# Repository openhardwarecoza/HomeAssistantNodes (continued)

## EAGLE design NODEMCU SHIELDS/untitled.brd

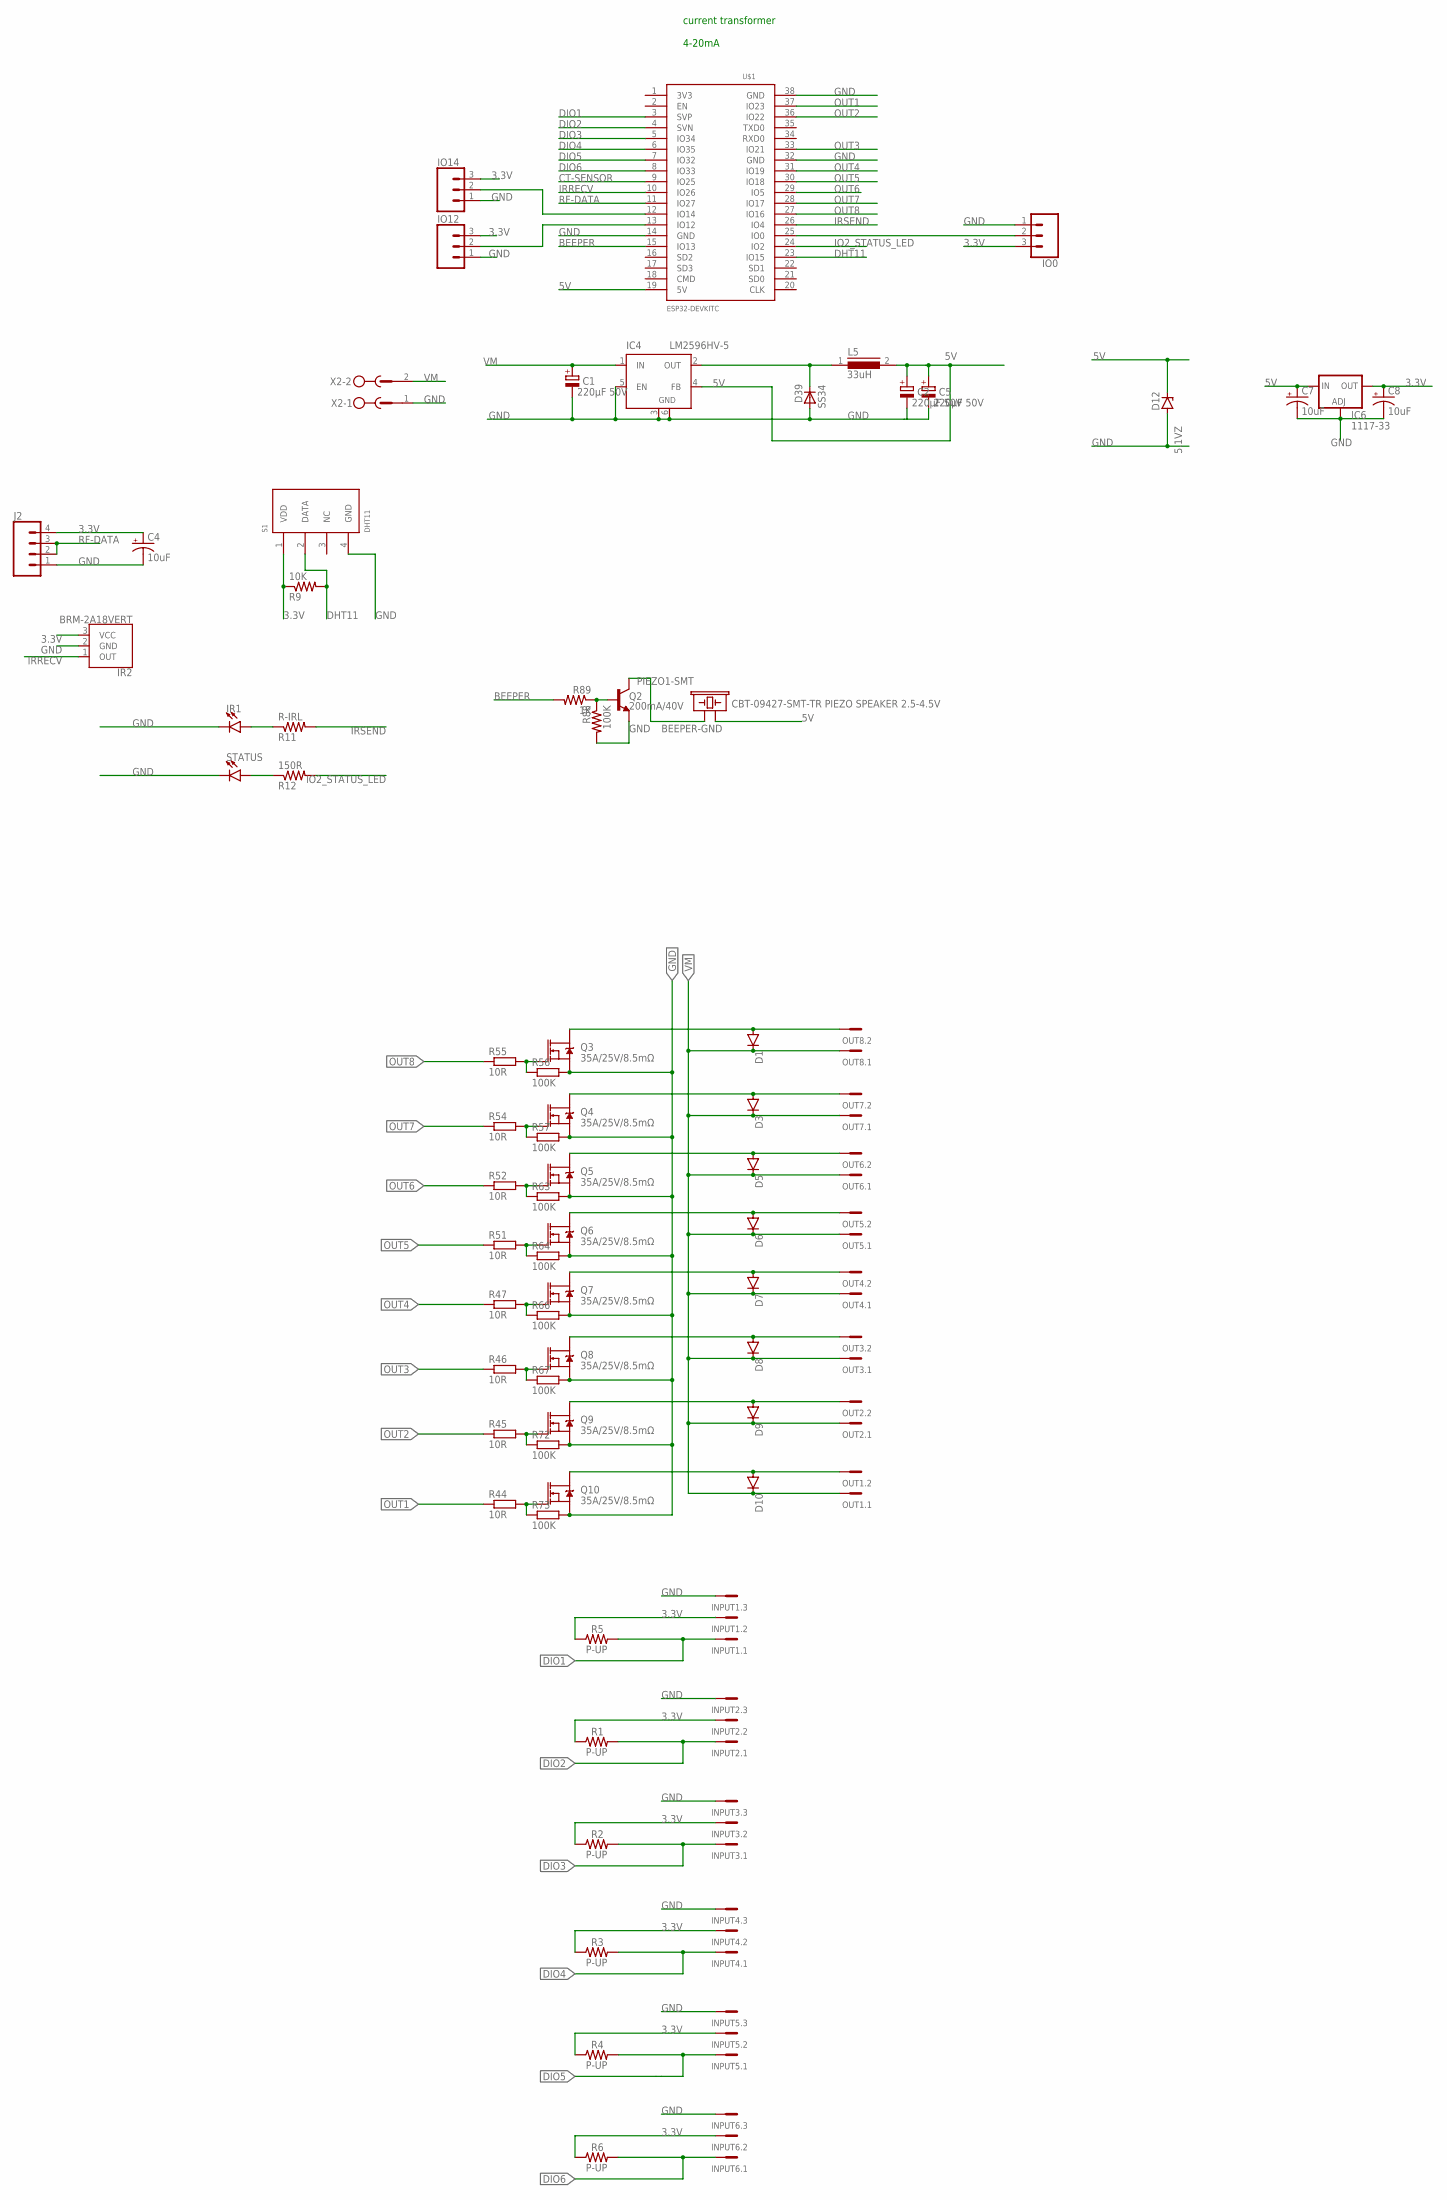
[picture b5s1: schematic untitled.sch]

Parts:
C1, C2, C5: 220µF 50V; E3,5-8
C4, C7, C8: 10uF; CPOL-RADIAL-10UF-25V
D1, D3, D5, D6, D7, D8, D9, D10: 1N4148DO35-7; DO35-7
D12: 5.1VZ; SMB
D39: SS34; SOD87
IC4: LM2596HV-5; TO263-5
IC6: 1117-33; SOT223
INPUT1, INPUT2, INPUT3, INPUT4, INPUT5, INPUT6: MCV3
IO0, IO12, IO14: CONN_03LOCK; 1X03_LOCK
IR1: LED3MM; LED_3MM
IR2: BRM-2A18VERT; BRM-2508_VERT
J2: CONN_04LOCK; 1X04_LOCK
L5: 33uH; DR127
OUT1, OUT2, OUT3, OUT4, OUT5, OUT6, OUT7, OUT8: MCV2
PIEZO1-SMT: CBT-09427-SMT-TR PIEZO SPEAKER 2.5-4.5V; BUZZER-12MM
Q2: 200mA/40V; TO-92
Q3, Q4, Q5, Q6, Q7, Q8, Q9, Q10: 35A/25V/8.5mΩ; DPAK
R1, R2, R3, R4, R5, R6: P-UP; 0204/7
R9: 10K; 0204/7
R11: R-IRL; 0204/7
R12: 150R; 0204/7
R44, R45, R46, R47, R51, R52, R54, R55: 10R; 0204/7
R56, R57, R63, R64, R66, R67, R72, R73, R88: 100K; 0204/7
R89: 1K; 0204/7
S1: DHT11
STATUS: LED3MM; LED_3MM
U$1: ESP32NODEMCU
X2: MSTBV2

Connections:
3.3V: C4.1 (+), C8.1 (+), IC6.4 (OUT), INPUT1.2, INPUT2.2, INPUT3.2, INPUT4.2, INPUT5.2, INPUT6.2, IO0.3, IO12.3, IO14.3, IR2.3 (VCC), J2.4, R1.1, R2.1, R3.1, R4.1, R5.1, R6.1, R9.1, S1.1 (VDD)
5V: C2.+, C5.+, C7.1 (+), D12.C, IC4.4 (FB), IC6.3 (IN), L5.2, PIEZO1-SMT.+ (1), U$1.19 (5V)
BEEPER: R89.2, U$1.15 (IO13)
BEEPER-GND: PIEZO1-SMT.- (2), Q2.3 (C)
CT-SENSOR: U$1.9 (IO25)
DHT11: R9.2, S1.2 (DATA), U$1.23 (IO15)
DIO1: INPUT1.1, R5.2, U$1.3 (SVP)
DIO2: INPUT2.1, R1.2, U$1.4 (SVN)
DIO3: INPUT3.1, R2.2, U$1.5 (IO34)
DIO4: INPUT4.1, R3.2, U$1.6 (IO35)
DIO5: INPUT5.1, R4.2, U$1.7 (IO32)
DIO6: INPUT6.1, R6.2, U$1.8 (IO33)
GND: C1.-, C2.-, C4.2 (-), C5.-, C7.2 (-), C8.2 (-), D12.A, D39.2 (A), IC4.3 (GND), IC4.5 (EN), IC4.6 (GND), IC6.1 (ADJ), INPUT1.3, INPUT2.3, INPUT3.3, INPUT4.3, INPUT5.3, INPUT6.3, IO0.1, IO12.1, IO14.1, IR1.K (C), IR2.2 (GND), J2.1, Q2.1 (E), Q3.3 (S), Q4.3 (S), Q5.3 (S), Q6.3 (S), Q7.3 (S), Q8.3 (S), Q9.3 (S), Q10.3 (S), R56.2, R57.2, R63.2, R64.2, R66.2, R67.2, R72.2, R73.2, R88.2, S1.4 (GND), STATUS.K (C), U$1.14 (GND), U$1.32 (GND), U$1.38 (GND), X2.1
IO2_STATUS_LED: R12.2, U$1.24 (IO2)
IRRECV: IR2.1 (OUT), U$1.10 (IO26)
IRSEND: R11.2, U$1.26 (IO4)
unnamed: R12.1, STATUS.A
unnamed: IO0.2, U$1.25 (IO0)
unnamed: IO12.2, U$1.13 (IO12)
unnamed: IO14.2, U$1.12 (IO14)
unnamed: D9.A, OUT2.2, Q9.4 (D)
unnamed: IR1.A, R11.1
unnamed: Q2.2 (B), R88.1, R89.1
unnamed: Q10.1 (G), R44.2, R73.1
unnamed: Q9.1 (G), R45.2, R72.1
unnamed: Q8.1 (G), R46.2, R67.1
unnamed: Q7.1 (G), R47.2, R66.1
unnamed: Q6.1 (G), R51.2, R64.1
unnamed: Q5.1 (G), R52.2, R63.1
unnamed: Q4.1 (G), R54.2, R57.1
unnamed: Q3.1 (G), R55.2, R56.1
unnamed: D1.A, OUT8.2, Q3.4 (D)
unnamed: D3.A, OUT7.2, Q4.4 (D)
unnamed: D5.A, OUT6.2, Q5.4 (D)
unnamed: D6.A, OUT5.2, Q6.4 (D)
unnamed: D7.A, OUT4.2, Q7.4 (D)
unnamed: D10.A, OUT1.2, Q10.4 (D)
unnamed: D8.A, OUT3.2, Q8.4 (D)
unnamed: D39.1 (C), IC4.2 (OUT), L5.1
OUT1: R44.1, U$1.37 (IO23)
OUT2: R45.1, U$1.36 (IO22)
OUT3: R46.1, U$1.33 (IO21)
OUT4: R47.1, U$1.31 (IO19)
OUT5: R51.1, U$1.30 (IO18)
OUT6: R52.1, U$1.29 (IO5)
OUT7: R54.1, U$1.28 (IO17)
OUT8: R55.1, U$1.27 (IO16)
RF-DATA: J2.2, J2.3, U$1.11 (IO27)
VM: C1.+, D1.C, D3.C, D5.C, D6.C, D7.C, D8.C, D9.C, D10.C, IC4.1 (IN), OUT1.1, OUT2.1, OUT3.1, OUT4.1, OUT5.1, OUT6.1, OUT7.1, OUT8.1, X2.2

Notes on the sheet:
current transformer 4-20mA

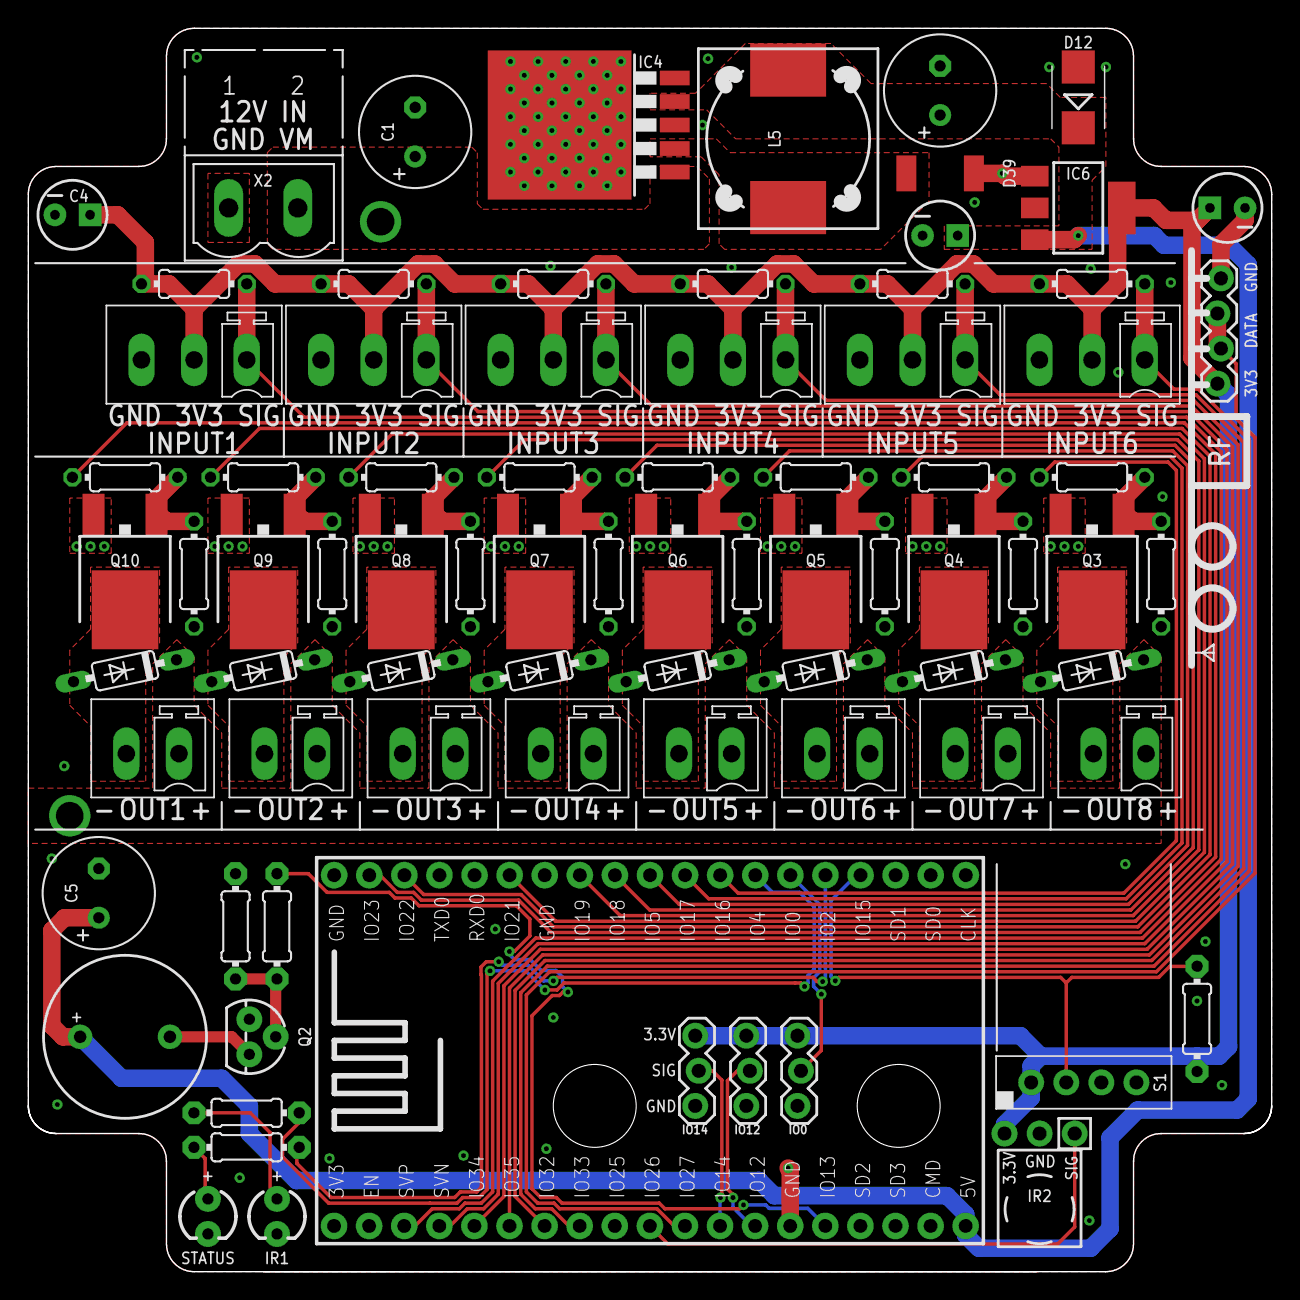
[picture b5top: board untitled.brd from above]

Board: 2 copper layers, 90.0 x 90.0 mm, 80 parts (0 on the bottom side), 48 nets.

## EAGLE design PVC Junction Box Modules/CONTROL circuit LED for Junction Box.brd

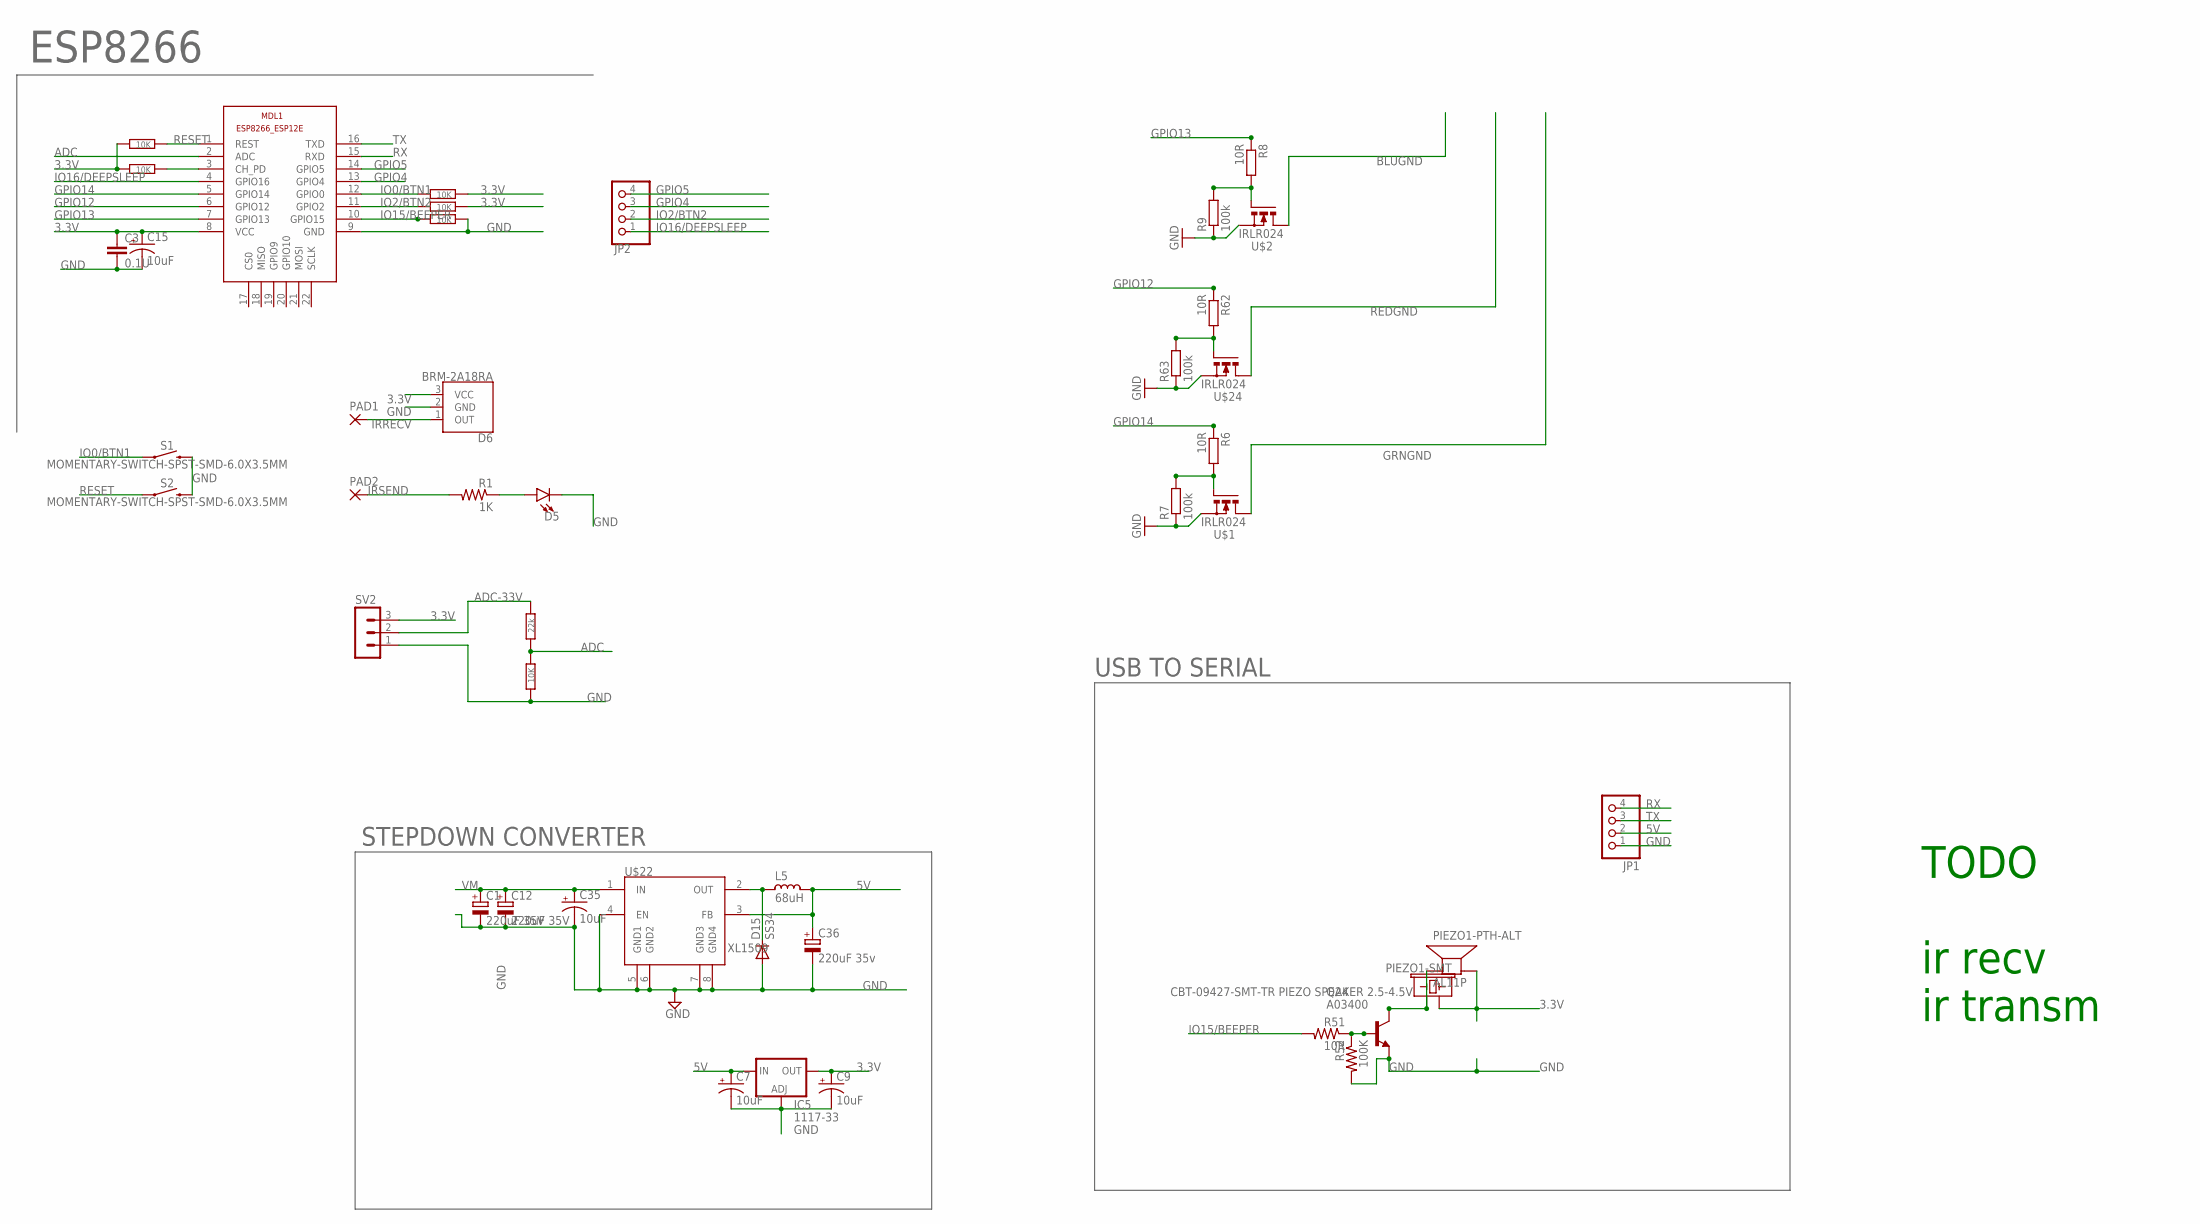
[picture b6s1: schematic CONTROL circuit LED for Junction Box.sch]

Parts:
C1, C12: 220uF 35V; E3,5-8
C3: 0.1U; C1206
C7, C9, C15, C35: 10uF; EIA3216
C36: 220uF 35v; E3,5-8
D5: LED3MM; LED_3MM
D6: BRM-2A18RA; BRM-2508
D15: SS34; DO-214AC
IC5: 1117-33; SOT223
JP1, JP2: PINHD-1X4; 1X04
L5: 68uH; CD75
MDL1: ESP8266-12EESP8266-ESP12E; ESP8266-ESP12E
PAD1, PAD2: 1,6/0,9
PIEZO1-PTH-ALT: AL11P
PIEZO1-SMT: CBT-09427-SMT-TR PIEZO SPEAKER 2.5-4.5V; BUZZER-CCV
Q24: A03400; SOT23-BEC
R1: 1K; M1206
R3: 22k; R1206
R4, R11, R12, R28, R29, R31: 10K; R1206
R6, R8, R51, R62: 10R; R1206
R7, R9, R63: 100k; R1206
R52: 100K; R1206
S1, S2: MOMENTARY-SWITCH-SPST-SMD-6.0X3.5MM; TACTILE_SWITCH_SMD_6.0X3.5MM
SV2: MA03-1
U$1, U$2, U$24: IRLR024; D-PAK_TO252AA
U$22: XL1509; SO08

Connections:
3.3V: C3.1, C9.A (+), C15.A (+), D6.3 (VCC), IC5.4 (OUT), MDL1.8 (VCC), PIEZO1-PTH-ALT.-, PIEZO1-SMT.+ (1), R11.2, R12.2, R28.1, R29.1, SV2.3
5V: C7.A (+), C36.+, IC5.3 (IN), JP1.2, L5.1, U$22.3 (FB)
ADC: MDL1.2 (ADC), R3.1, R4.2
ADC-33V: R3.2, SV2.2
BEEPER-GND: PIEZO1-PTH-ALT.+, PIEZO1-SMT.- (2), Q24.C
BLUGND: U$2.4 (D)
GND: C1.-, C3.2, C7.C (-), C9.C (-), C12.-, C15.C (-), C35.C (-), C36.-, D5.K (C), D6.2 (GND), D15.2 (A), IC5.1 (ADJ), JP1.1, MDL1.9 (GND), Q24.E, R4.1, R7.1, R9.1, R31.2, R52.2, R63.1, S1.2, S2.2, SV2.1, U$1.3 (S), U$2.3 (S), U$22.4 (EN), U$22.5 (GND1), U$22.6 (GND2), U$22.7 (GND3), U$22.8 (GND4), U$24.3 (S)
GPIO4: JP2.3, MDL1.13 (GPIO4)
GPIO5: JP2.4, MDL1.14 (GPIO5)
GPIO12: MDL1.6 (GPIO12), R62.1
GPIO13: MDL1.7 (GPIO13), R8.1
GPIO14: MDL1.5 (GPIO14), R6.1
GRNGND: U$1.4 (D)
IO0/BTN1: MDL1.12 (GPIO0), R12.1, S1.1
IO2/BTN2: JP2.2, MDL1.11 (GPIO2), R11.1
IO15/BEEPER: MDL1.10 (GPIO15), R31.1, R51.2
IO16/DEEPSLEEP: JP2.1, MDL1.4 (GPIO16)
IRRECV: D6.1 (OUT), PAD1.1
IRSEND: PAD2.1, R1.2
unnamed: R62.2, R63.2, U$24.1 (G)
unnamed: D15.1 (C), L5.2, U$22.2 (OUT)
unnamed: R6.2, R7.2, U$1.1 (G)
unnamed: R8.2, R9.2, U$2.1 (G)
unnamed: D5.A, R1.1
unnamed: MDL1.3 (CH_PD), R28.2
unnamed: Q24.B, R51.1, R52.1
REDGND: U$24.4 (D)
RESET: MDL1.1 (REST), R29.2, S2.1
RX: JP1.4, MDL1.15 (RXD)
TX: JP1.3, MDL1.16 (TXD)
VM: C1.+, C12.+, C35.A (+), U$22.1 (IN)

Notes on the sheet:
ESP8266
STEPDOWN CONVERTER
USB TO SERIAL
TODO ir recv ir transm

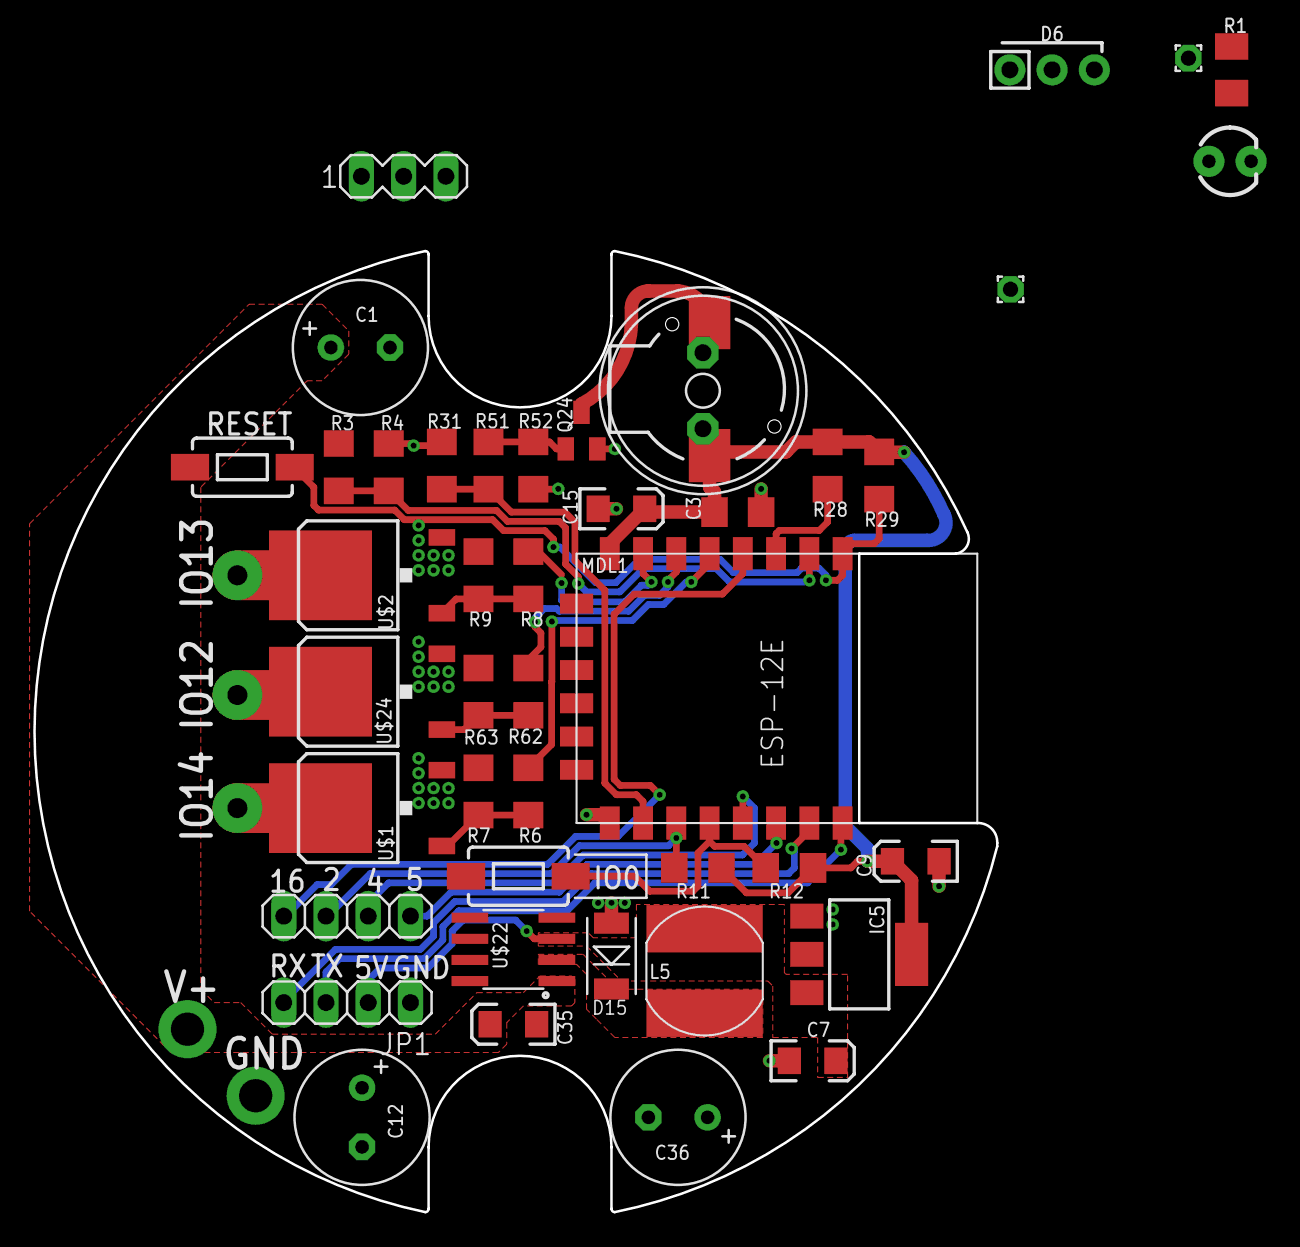
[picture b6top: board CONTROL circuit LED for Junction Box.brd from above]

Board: 2 copper layers, 57.9 x 57.8 mm, 44 parts (1 on the bottom side), 28 nets.

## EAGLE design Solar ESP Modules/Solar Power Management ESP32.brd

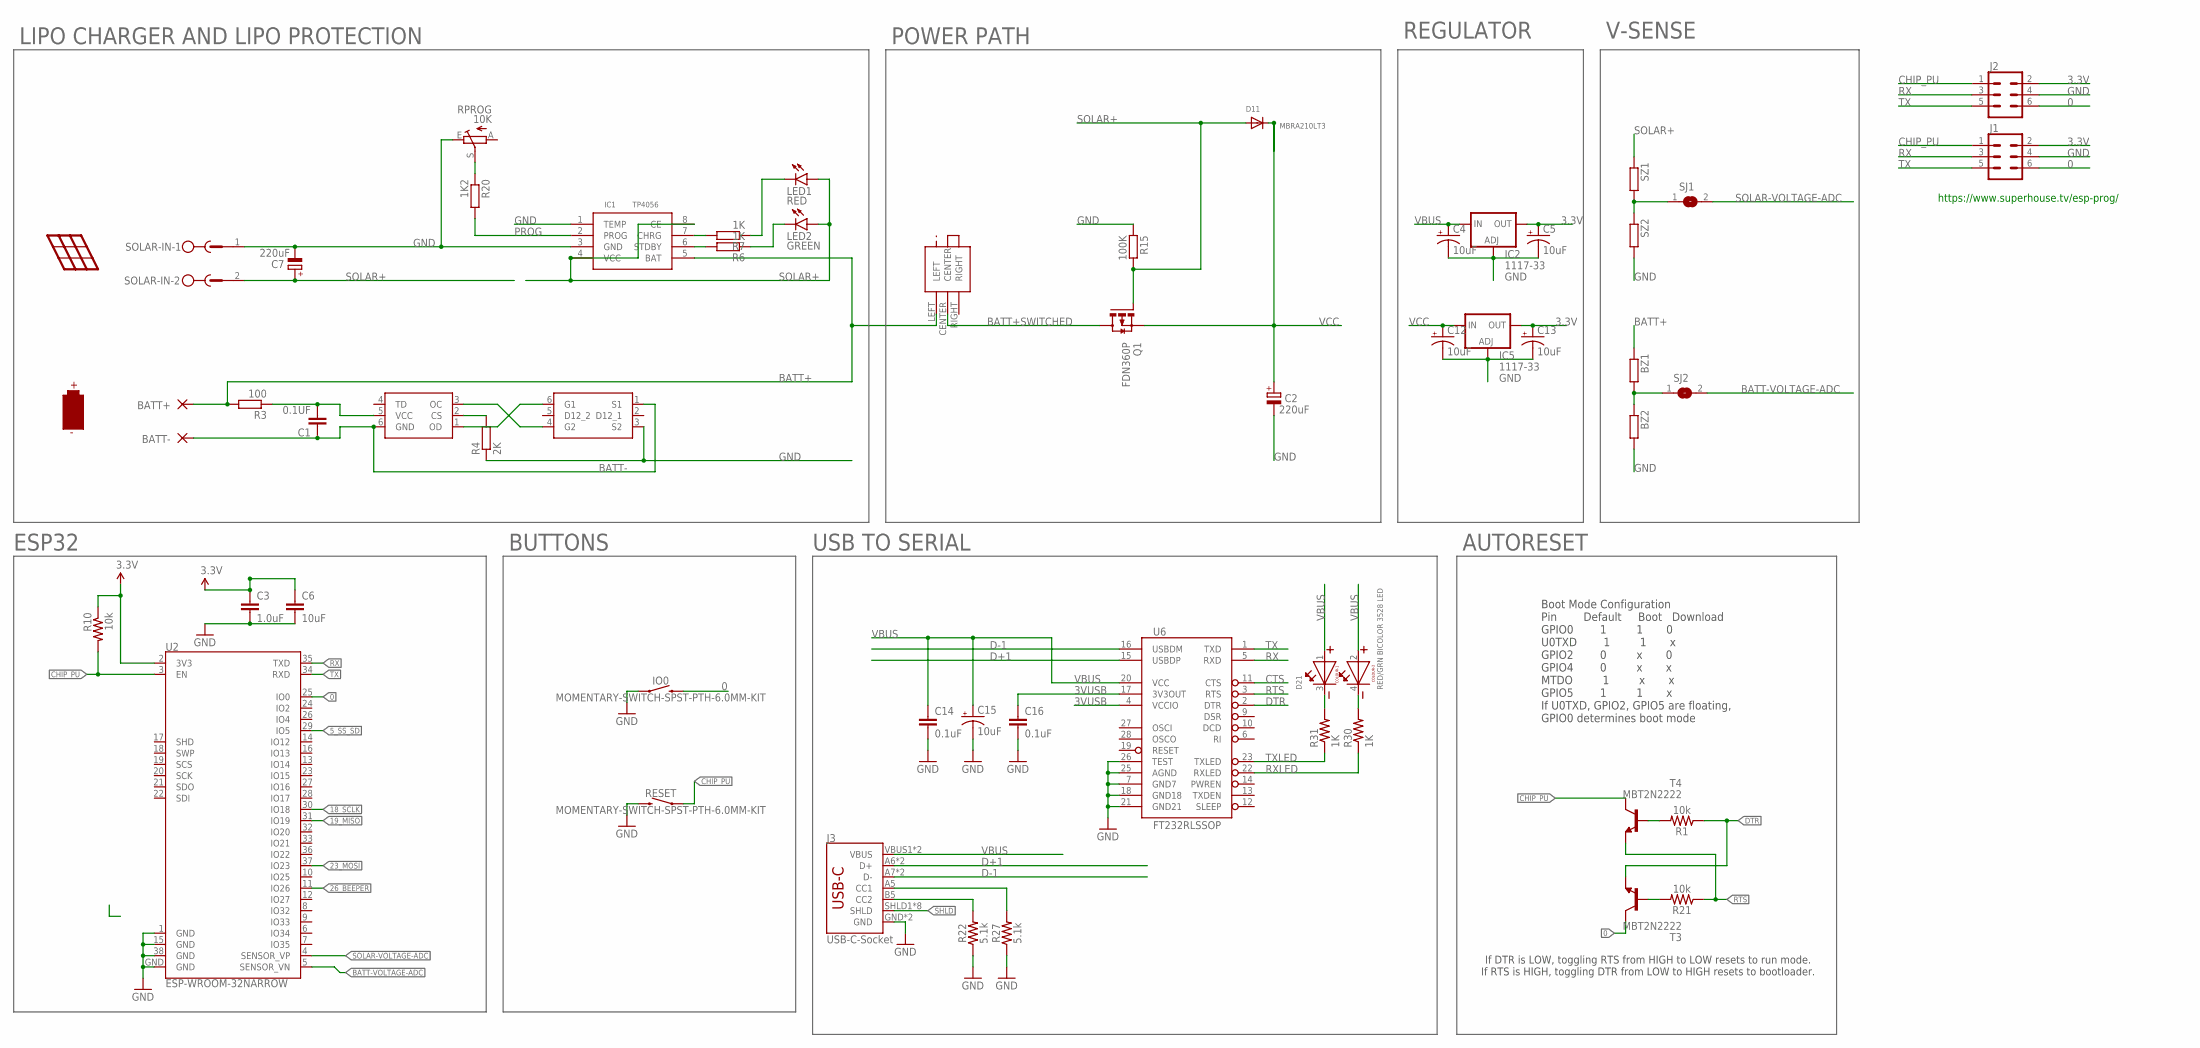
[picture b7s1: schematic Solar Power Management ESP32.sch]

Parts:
BATT+: 3,81/1,4
BATT-: 3,81/1,4
BZ1, BZ2: R-EU_R1206; R1206
C1: 0.1UF; C1206
C2, C7: 220uF; E3,5-8
C3: 1.0uF; 1206
C4, C5, C12, C13, C15: 10uF; EIA3216
C6: 10uF; 1206
C14, C16: 0.1uF; 0603-CAP
D11: MBRA210LT3; SMADIODE
D21: RED/GRN BICOLOR 3528 LED; 3528
IC1: TP4056; SOP-8
IC2, IC5: 1117-33; SOT223
IO0: MOMENTARY-SWITCH-SPST-PTH-6.0MM-KIT; TACTILE_SWITCH_PTH_6.0MM_KIT
J1, J2: CONN_03X2SHROUD; 2X3-SHROUDED
J3: USB-C-Socket; USB-C-16P
LED1: RED; CHIPLED_1206
LED2: GREEN; CHIPLED_1206
Q1: FDN360P; SUPER-SOT3
R1, R21: 10k; 0603
R3: 100; R1206
R4: 2K; R1206
R6, R7: 1K; R1206
R10: 10k; R1206
R15: 100K; R1206
R20: 1K2; R1206
R22, R27: 5.1k; 0603@1
R30, R31: 1K; 0603-RES
RESET: MOMENTARY-SWITCH-SPST-PTH-6.0MM-KIT; TACTILE_SWITCH_PTH_6.0MM_KIT
RPROG: 10K; B25P
SJ1, SJ2: SJ
SOLAR-IN: MSTBV2
SZ1, SZ2: R-EU_R1206; R1206
T3, T4: MBT2N2222; SOT23-BEC
U2: ESP-WROOM-32NARROW; ESP-WROOM-32-NARROW
U6: FT232RLSSOP; SSOP28DB
U$1: FS312F-G; SOT23-6
U$2: FS8205; SOT23-6
U$3: XKBENTERPRISESS-12D11G5R

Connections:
0: IO0.3 (2), J1.6, J2.6, T3.C, U2.25 (IO0)
3.3V: C3.1, C5.A (+), C6.1, C13.A (+), IC2.4 (OUT), IC5.4 (OUT), J1.2, J2.2, R10.1, U2.2 (3V3)
3VUSB: C16.1, U6.4 (VCCIO), U6.17 (3V3OUT)
5_SS_SD: U2.29 (IO5)
18_SCLK: U2.30 (IO18)
19_MISO: U2.31 (IO19)
23_MOSI: U2.37 (IO23)
26_BEEPER: U2.11 (IO26)
BATT+: BATT+.1, BZ1.1, IC1.5 (BAT), R3.2, U$3.LEFT
BATT+SWITCHED: Q1.3 (D), U$3.CENTER
BATT-: BATT-.1, C1.1, U$1.6 (GND), U$2.1 (S1)
BATT-VOLTAGE-ADC: BZ1.2, BZ2.1, SJ2.1, SJ2.2, U2.5 (SENSOR_VN)
CC1: J3.A5 (CC1), R27.2
CC2: J3.B5 (CC2), R22.2
CHG: IC1.7 (CHRG), R7.2
CHIP_PU: J1.1, J2.1, R10.2, RESET.1, T4.C, U2.3 (EN)
CTS: U6.11 (CTS)
D+1: J3.A6 (D+), J3.B6 (D+), U6.15 (USBDP)
D-1: J3.A7 (D-), J3.B7 (D-), U6.16 (USBDM)
DTR: R1.1, T3.E, U6.2 (DTR)
GND: BZ2.2, C2.-, C3.2, C4.C (-), C5.C (-), C6.2, C7.-, C12.C (-), C13.C (-), C14.2, C15.C (-), C16.2, IC1.1 (TEMP), IC1.3 (GND), IC2.1 (ADJ), IC5.1 (ADJ), IO0.1, J1.4, J2.4, J3.GND, J3.GND2 (GND), R4.1, R15.1, R22.1, R27.1, RESET.3 (2), RPROG.E, SOLAR-IN.1, SZ2.2, U2.1 (GND), U2.15 (GND), U2.38 (GND), U2.GND, U6.7 (GND7), U6.18 (GND18), U6.21 (GND21), U6.25 (AGND), U6.26 (TEST), U$2.3 (S2)
LEDCHR: LED1.C, R7.1
LEDSBY: LED2.C, R6.1
unnamed: R4.2, U$1.2 (CS)
unnamed: R1.2, T4.B
unnamed: R21.2, T3.B
unnamed: D21.4 (C2), R30.2
unnamed: D21.3 (C1), R31.2
unnamed: R20.1, RPROG.S
OC: U$1.3 (OC), U$2.4 (G2)
OD: U$1.1 (OD), U$2.6 (G1)
PROG: IC1.2 (PROG), R20.2
RTS: R21.1, T4.E, U6.3 (RTS)
RX: J1.3, J2.3, U2.35 (TXD), U6.5 (RXD)
RXLED: R30.1, U6.22 (RXLED)
SHLD: J3.SHLD1 (SHLD), J3.SHLD2 (SHLD), J3.SHLD3 (SHLD), J3.SHLD4 (SHLD), J3.SHLD5 (SHLD), J3.SHLD6 (SHLD), J3.SHLD7 (SHLD), J3.SHLD8 (SHLD)
SOLAR+: C7.+, D11.A, IC1.4 (VCC), IC1.8 (CE), LED1.A, LED2.A, Q1.1 (G), R15.2, SOLAR-IN.2, SZ1.1
SOLAR-VOLTAGE-ADC: SJ1.1, SJ1.2, SZ1.2, SZ2.1, U2.4 (SENSOR_VP)
STANDBY: IC1.6 (STDBY), R6.2
TX: J1.5, J2.5, U2.34 (RXD), U6.1 (TXD)
TXLED: R31.1, U6.23 (TXLED)
VBUS: C4.A (+), C14.1, C15.A (+), D21.1 (A1), D21.2 (A2), IC2.3 (IN), J3.VBUS1 (VBUS), J3.VBUS2 (VBUS), U6.20 (VCC)
VCC: C2.+, C12.A (+), D11.C, IC5.3 (IN), Q1.2 (S)
VCC-PROT: C1.2, R3.1, U$1.5 (VCC)

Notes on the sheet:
ESP32
BUTTONS
LIPO CHARGER AND LIPO PROTECTION
POWER PATH
REGULATOR
V-SENSE
Boot Mode Configuration Pin Default Boot Download GPIO0 1 1 0 U0TXD 1 1 x GPIO2 0 x 0 GPIO4 0 x x MTDO 1 x x GPIO5 1 1 x If U0TXD, GPIO2, GPIO5 are floating, GPIO0 determines boot mode
If DTR is LOW, toggling RTS from HIGH to LOW resets to run mode. If RTS is HIGH, toggling DTR from LOW to HIGH resets to bootloader.
USB TO SERIAL
AUTORESET
https://www.superhouse.tv/esp-prog/

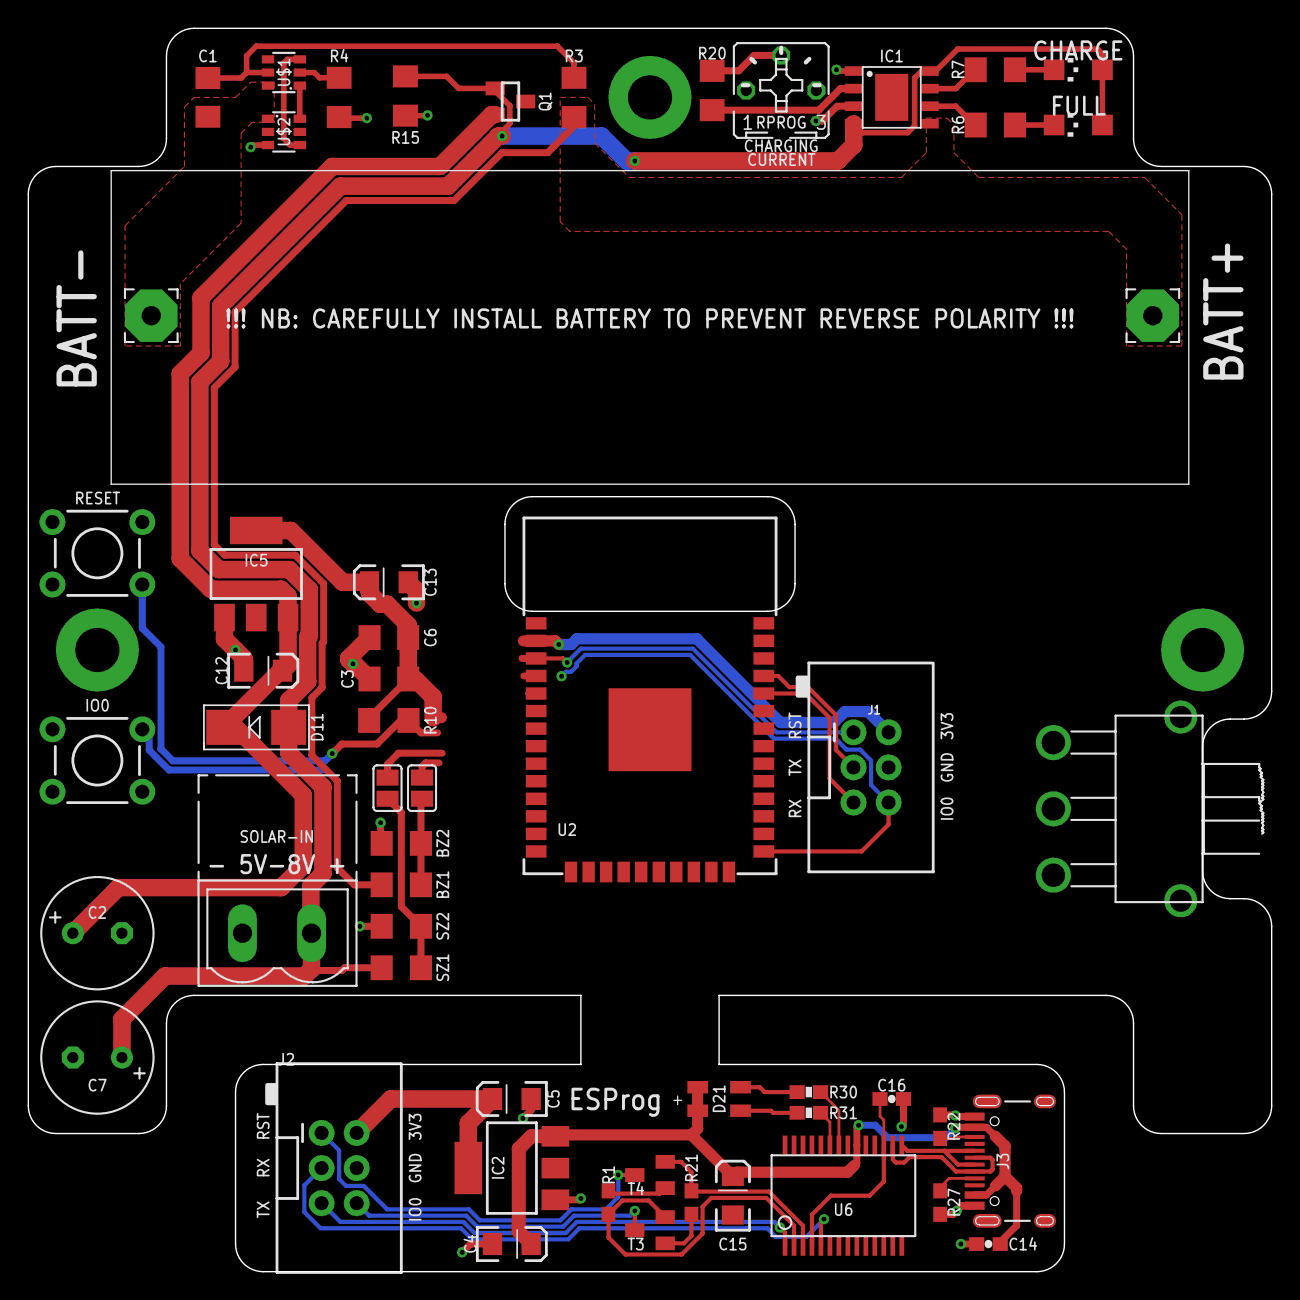
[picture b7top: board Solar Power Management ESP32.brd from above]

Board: 2 copper layers, 90.0 x 90.0 mm, 55 parts (0 on the bottom side), 38 nets.
